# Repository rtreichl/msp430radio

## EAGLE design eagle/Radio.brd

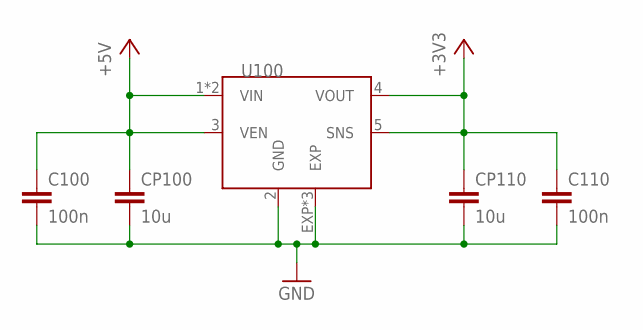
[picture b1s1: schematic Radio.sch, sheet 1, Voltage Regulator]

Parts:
C100, C110: 100n; C1206K
CP100, CP110: 10u; C1206K
U100: LP38693; LP38693_WSON

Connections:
+3V3: C110.1, CP110.1, U100.4 (VOUT), U100.5 (SNS); also elsewhere on the board
+5V: C100.1, CP100.1, U100.1 (VIN), U100.3 (VEN), U100.6 (VIN); also elsewhere on the board
GND: C100.2, C110.2, CP100.2, CP110.2, U100.2 (GND), U100.EXP, U100.EXP1 (EXP), U100.EXP2 (EXP); also elsewhere on the board

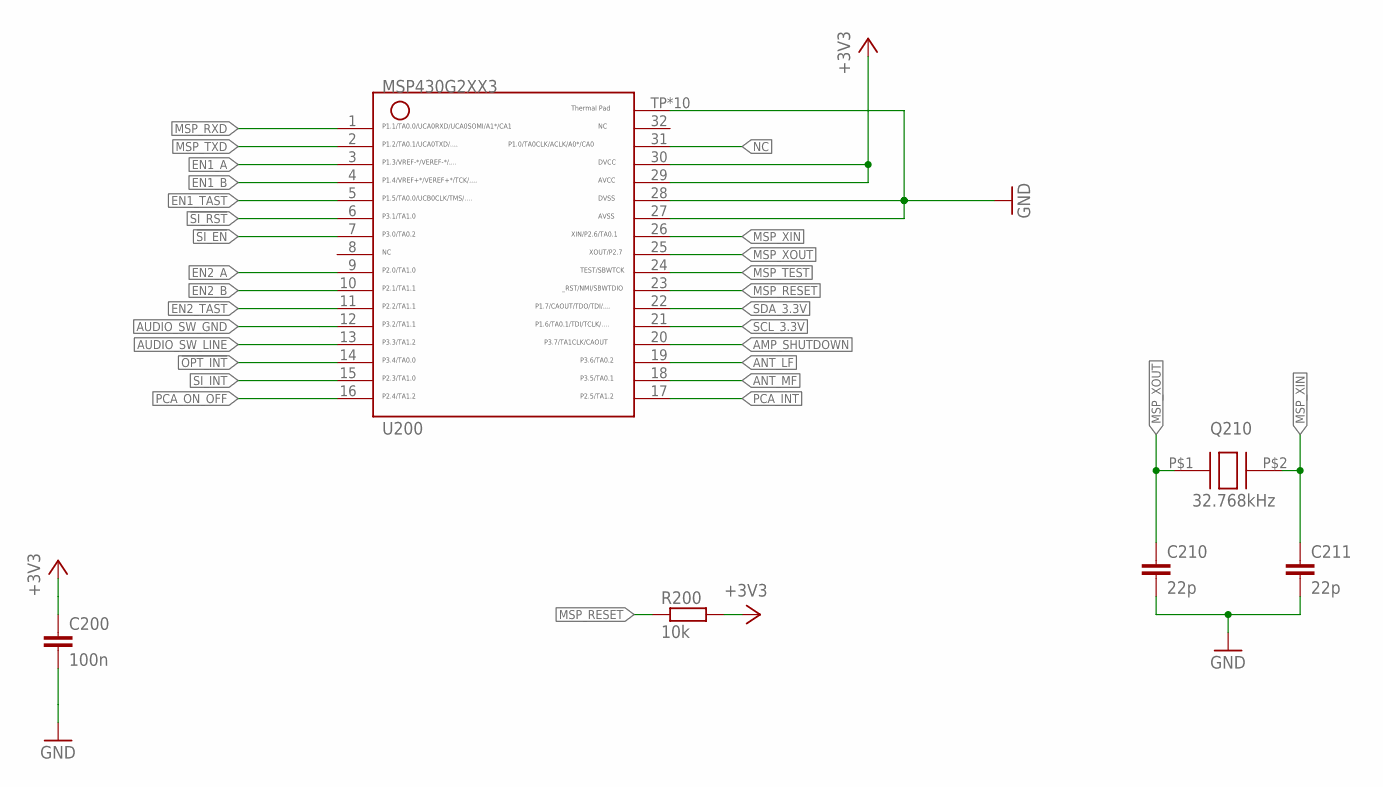
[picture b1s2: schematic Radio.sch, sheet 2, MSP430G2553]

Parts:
C200: 100n; C1206K
C210, C211: 22p; C1206K
Q210: 32.768kHz; CM7V-T1A
R200: 10k; R1206
U200: MSP430G2553; RHB32

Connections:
!OPT_INT: U200.14; also elsewhere on the board
!SI_EN: U200.7; also elsewhere on the board
!SI_RST: U200.6; also elsewhere on the board
+3V3: C200.1, R200.2, U200.29, U200.30; also elsewhere on the board
AMP_SHUTDOWN: U200.20; also elsewhere on the board
ANT_LF: U200.19; also elsewhere on the board
ANT_MF: U200.18; also elsewhere on the board
AUDIO_SW_GND: U200.12; also elsewhere on the board
AUDIO_SW_LINE: U200.13; also elsewhere on the board
EN1_A: U200.3; also elsewhere on the board
EN1_B: U200.4; also elsewhere on the board
EN1_TAST: U200.5; also elsewhere on the board
EN2_A: U200.9; also elsewhere on the board
EN2_B: U200.10; also elsewhere on the board
EN2_TAST: U200.11; also elsewhere on the board
GND: C200.2, C210.2, C211.2, U200.27, U200.28, U200.TP, U200.TP1 (TP), U200.TP2 (TP), U200.TP3 (TP), U200.TP4 (TP), U200.TP5 (TP), U200.TP6 (TP), U200.TP7 (TP), U200.TP8 (TP), U200.TP9 (TP); also elsewhere on the board
MSP_RESET: R200.1, U200.23; also elsewhere on the board
MSP_RXD: U200.1; also elsewhere on the board
MSP_TEST: U200.24; also elsewhere on the board
MSP_TXD: U200.2; also elsewhere on the board
MSP_XIN: C211.1, Q210.P$2 (2), U200.26
MSP_XOUT: C210.1, Q210.P$1 (1), U200.25
NC: U200.31
PCA_INT: U200.17; also elsewhere on the board
PCA_ON_OFF: U200.16; also elsewhere on the board
SCL_3.3V: U200.21; also elsewhere on the board
SDA_3.3V: U200.22; also elsewhere on the board
SI_INT: U200.15; also elsewhere on the board

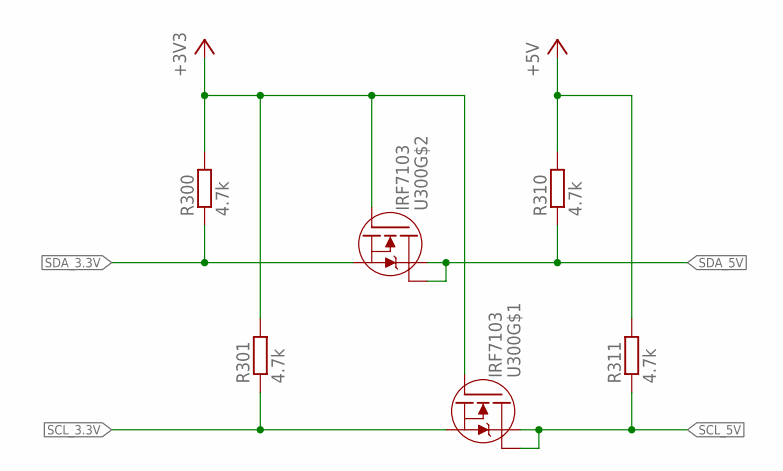
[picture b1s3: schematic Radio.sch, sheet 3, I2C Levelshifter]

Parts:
R300, R301, R310, R311: 4.7k; R1206
U300: IRF7103; SO8-2

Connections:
+3V3: R300.2, R301.2, U300.2 (G), U300.4 (G); also elsewhere on the board
+5V: R310.2, R311.2; also elsewhere on the board
SCL_3.3V: R301.1, U300.1 (S); also elsewhere on the board
SCL_5V: R311.1, U300.7 (D), U300.8 (D); also elsewhere on the board
SDA_3.3V: R300.1, U300.3 (S); also elsewhere on the board
SDA_5V: R310.1, U300.5 (D), U300.6 (D); also elsewhere on the board

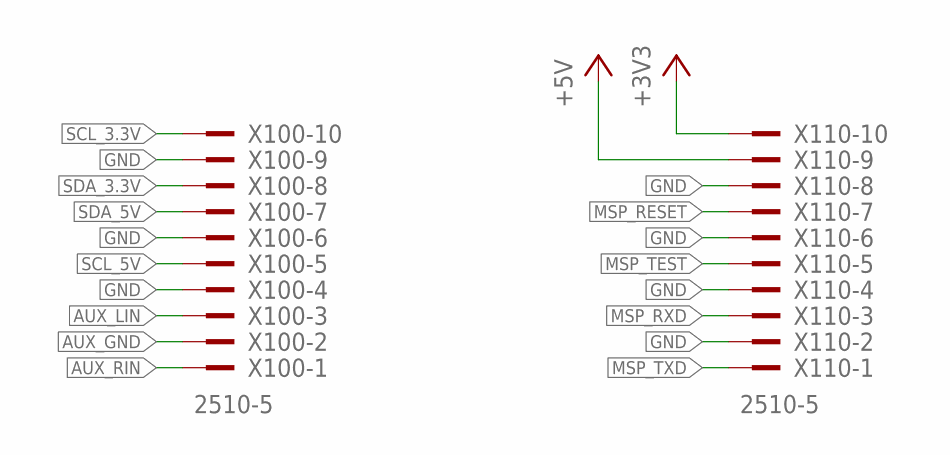
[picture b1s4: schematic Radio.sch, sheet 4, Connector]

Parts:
X100, X110: 2510-5; PAK100/2500-5-10

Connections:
+3V3: X110.10; also elsewhere on the board
+5V: X110.9; also elsewhere on the board
AUX_GND: X100.2; also elsewhere on the board
AUX_LIN: X100.3; also elsewhere on the board
AUX_RIN: X100.1; also elsewhere on the board
GND: X100.4, X100.6, X100.9, X110.2, X110.4, X110.6, X110.8; also elsewhere on the board
MSP_RESET: X110.7; also elsewhere on the board
MSP_RXD: X110.3; also elsewhere on the board
MSP_TEST: X110.5; also elsewhere on the board
MSP_TXD: X110.1; also elsewhere on the board
SCL_3.3V: X100.10; also elsewhere on the board
SCL_5V: X100.5; also elsewhere on the board
SDA_3.3V: X100.8; also elsewhere on the board
SDA_5V: X100.7; also elsewhere on the board

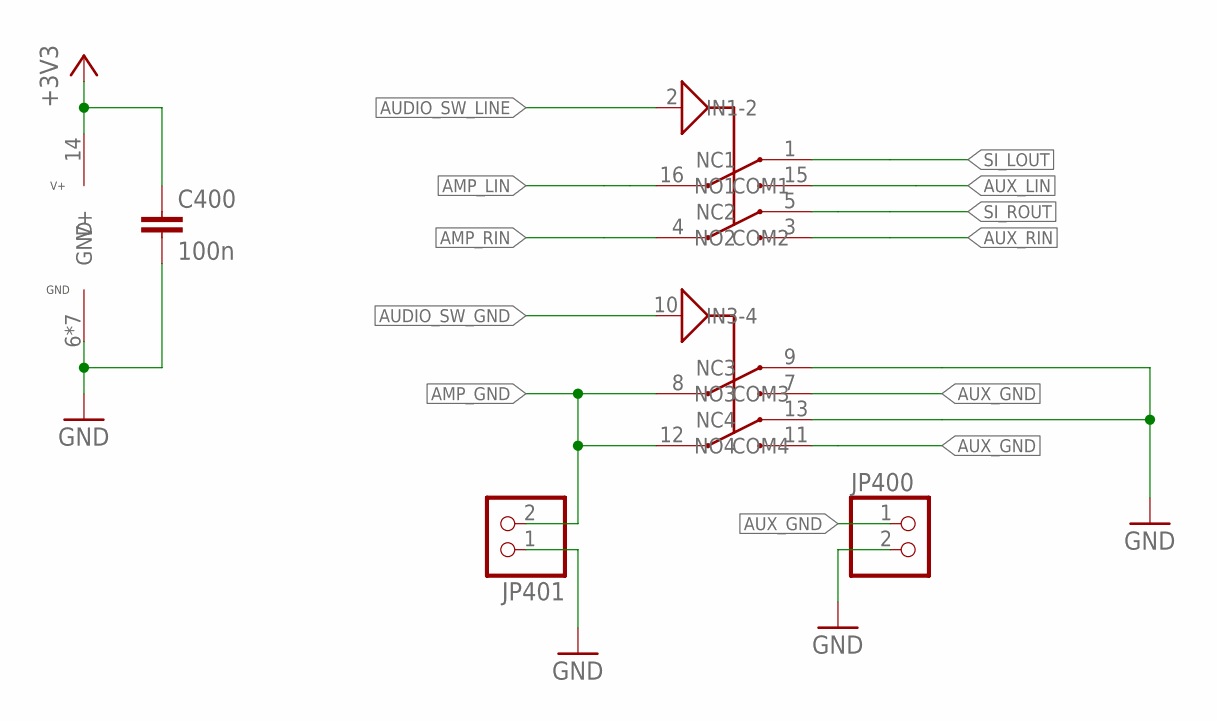
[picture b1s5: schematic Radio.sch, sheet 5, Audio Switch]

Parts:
C400: 100n; C1206K
JP400, JP401: PINHD-1X2; 1X02
U400: TS3A44159RGT; QFN16

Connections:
+3V3: C400.1, U400.14 (V+); also elsewhere on the board
AMP_GND: JP401.2, U400.8 (COM3), U400.12 (COM4); also elsewhere on the board
AMP_LIN: U400.16 (COM1); also elsewhere on the board
AMP_RIN: U400.4 (COM2); also elsewhere on the board
AUDIO_SW_GND: U400.10 (IN3-4); also elsewhere on the board
AUDIO_SW_LINE: U400.2 (IN1-2); also elsewhere on the board
AUX_GND: JP400.1, U400.7 (NO3), U400.11 (NO4); also elsewhere on the board
AUX_LIN: U400.15 (NO1); also elsewhere on the board
AUX_RIN: U400.3 (NO2); also elsewhere on the board
GND: C400.2, JP400.2, JP401.1, U400.6 (GND), U400.9 (NC3), U400.13 (NC4), U400.TH (GND), U400.TH1 (GND), U400.TH2 (GND), U400.TH3 (GND), U400.TH4 (GND), U400.TH5 (GND); also elsewhere on the board
SI_LOUT: U400.1 (NC1); also elsewhere on the board
SI_ROUT: U400.5 (NC2); also elsewhere on the board

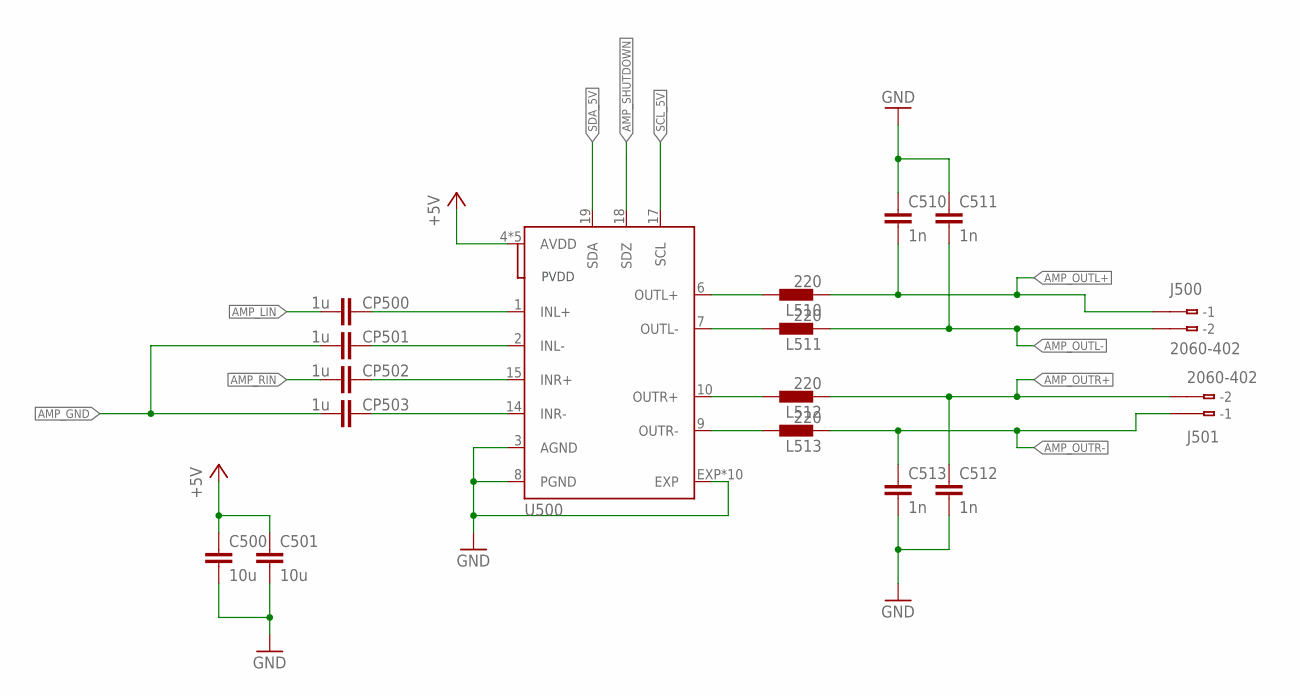
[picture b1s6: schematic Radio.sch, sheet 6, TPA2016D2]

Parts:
C500, C501: 10u; C1206K
C510, C511, C512, C513: 1n; C1206K
CP500, CP501, CP502, CP503: 1u; C1206K
J500, J501: 2060-402; WAGO_2060-402
L510, L511, L512, L513: 220; R0603
U500: TPA2016D2; TPA2016D2_PWQFN-20

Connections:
+5V: C500.1, C501.1, U500.4 (AVDD), U500.5 (AVDD), U500.11 (AVDD), U500.12 (AVDD), U500.13 (AVDD); also elsewhere on the board
AMP_GND: CP501.2, CP503.2; also elsewhere on the board
AMP_LIN: CP500.2; also elsewhere on the board
AMP_OUTL+: C510.2, J500.B-1, L510.1; also elsewhere on the board
AMP_OUTL-: C511.2, J500.B-2, L511.1; also elsewhere on the board
AMP_OUTR+: C512.1, J501.B-2, L512.1; also elsewhere on the board
AMP_OUTR-: C513.1, J501.B-1, L513.1; also elsewhere on the board
AMP_RIN: CP502.2; also elsewhere on the board
AMP_SHUTDOWN: U500.18 (SDZ); also elsewhere on the board
GND: C500.2, C501.2, C510.1, C511.1, C512.2, C513.2, U500.3 (AGND), U500.8 (PGND), U500.EXP, U500.EXP1 (EXP), U500.EXP2 (EXP), U500.EXP3 (EXP), U500.EXP4 (EXP), U500.EXP5 (EXP), U500.EXP6 (EXP), U500.EXP7 (EXP), U500.EXP8 (EXP), U500.EXP9 (EXP); also elsewhere on the board
unnamed: L510.2, U500.6 (OUTL+)
unnamed: L511.2, U500.7 (OUTL-)
unnamed: L512.2, U500.10 (OUTR+)
unnamed: L513.2, U500.9 (OUTR-)
unnamed: CP500.1, U500.1 (INL+)
unnamed: CP502.1, U500.15 (INR+)
unnamed: CP501.1, U500.2 (INL-)
unnamed: CP503.1, U500.14 (INR-)
SCL_5V: U500.17 (SCL); also elsewhere on the board
SDA_5V: U500.19 (SDA); also elsewhere on the board

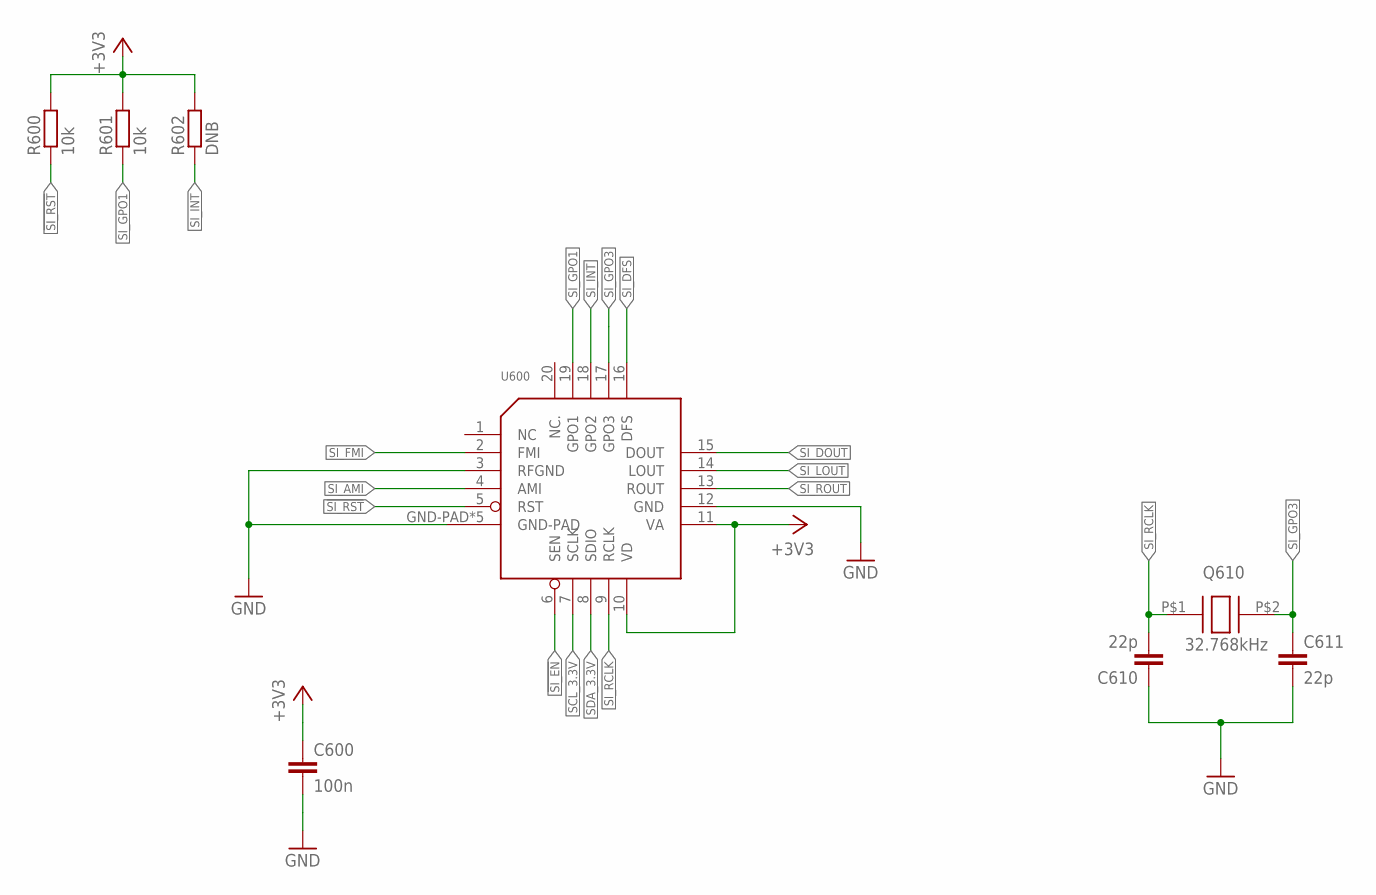
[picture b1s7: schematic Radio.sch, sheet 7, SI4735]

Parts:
C600: 100n; C1206K
C610, C611: 22p; C1206K
Q610: 32.768kHz; CM7V-T1A
R600, R601: 10k; R1206
R602: DNB; R1206
U600: SI473X-D60

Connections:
!SI_EN: U600.6 (SEN); also elsewhere on the board
!SI_RST: R600.1, U600.5 (RST); also elsewhere on the board
+3V3: C600.1, R600.2, R601.2, R602.2, U600.10 (VD), U600.11 (VA); also elsewhere on the board
GND: C600.2, C610.1, C611.2, U600.3 (RFGND), U600.12 (GND), U600.GND-PAD, U600.GND-PAD1 (GND-PAD), U600.GND-PAD2 (GND-PAD), U600.GND-PAD3 (GND-PAD), U600.GND-PAD4 (GND-PAD); also elsewhere on the board
SCL_3.3V: U600.7 (SCLK); also elsewhere on the board
SDA_3.3V: U600.8 (SDIO); also elsewhere on the board
SI_AMI: U600.4 (AMI); also elsewhere on the board
SI_DFS: U600.16 (DFS)
SI_DOUT: U600.15 (DOUT)
SI_FMI: U600.2 (FMI); also elsewhere on the board
SI_GPO1: R601.1, U600.19 (GPO1)
SI_GPO3: C611.1, Q610.P$2 (2), U600.17 (GPO3)
SI_INT: R602.1, U600.18 (GPO2); also elsewhere on the board
SI_LOUT: U600.14 (LOUT); also elsewhere on the board
SI_RCLK: C610.2, Q610.P$1 (1), U600.9 (RCLK)
SI_ROUT: U600.13 (ROUT); also elsewhere on the board

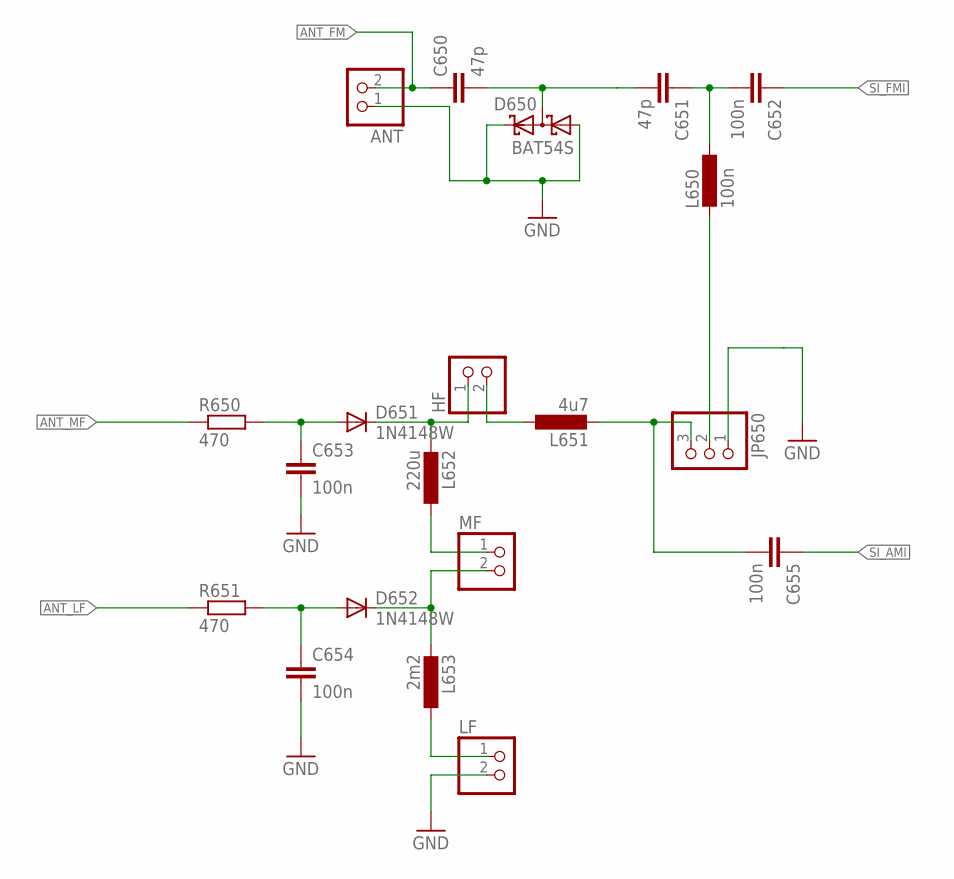
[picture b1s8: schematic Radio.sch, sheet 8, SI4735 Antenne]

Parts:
ANT: PINHD-1X2; 1X02
C650, C651: 47p; C1206K
C652, C653, C654, C655: 100n; C1206K
D650: BAT54S; SOT23
D651, D652: 1N4148W; SOD123
HF: PINHD-1X2; 1X02
JP650: PINHD-1X3; 1X03
L650: 100n; L1210
L651: 4u7; L1210
L652: 220u; L1210
L653: 2m2; L1812
LF: PINHD-1X2; 1X02
MF: PINHD-1X2; 1X02
R650, R651: 470; R1206

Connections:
ANT_FM: ANT.2, C650.1; also elsewhere on the board
ANT_LF: R651.1; also elsewhere on the board
ANT_MF: R650.1; also elsewhere on the board
GND: ANT.1, C653.2, C654.2, D650.1 (A1), D650.2 (C2), JP650.1, LF.2; also elsewhere on the board
unnamed: C650.2, C651.2, D650.3 (C1A2)
unnamed: HF.2, L651.1
unnamed: JP650.2, L650.2
unnamed: C655.2, JP650.3, L651.2
unnamed: D651.C, HF.1, L652.2
unnamed: D652.C, L653.2, MF.2
unnamed: C654.1, D652.A, R651.2
unnamed: C653.1, D651.A, R650.2
unnamed: L653.1, LF.1
unnamed: L652.1, MF.1
unnamed: C651.1, C652.2, L650.1
SI_AMI: C655.1; also elsewhere on the board
SI_FMI: C652.1; also elsewhere on the board

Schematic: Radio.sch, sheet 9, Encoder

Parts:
C800, C801, C802, C810, C811, C812: 10n; C1206K
EN800, EN810: PEC11R
R800, R801, R802, R803, R804, R805, R810, R811, R812, R813, R814, R815: 10k; R1206

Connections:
+3V3: R801.2, R803.2, R804.2, R811.1, R813.2, R814.2; also elsewhere on the board
EN1_A: C801.1, R802.2; also elsewhere on the board
EN1_B: C802.1, R805.2; also elsewhere on the board
EN1_TAST: C800.2, R800.1; also elsewhere on the board
EN2_A: C811.1, R812.2; also elsewhere on the board
EN2_B: C812.1, R815.2; also elsewhere on the board
EN2_TAST: C810.1, R810.2; also elsewhere on the board
GND: C800.1, C801.2, C802.2, C810.2, C811.2, C812.2, EN800.C, EN800.W, EN810.C, EN810.W; also elsewhere on the board
unnamed: EN810.A, R812.1, R813.1
unnamed: EN800.A, R802.1, R803.1
unnamed: EN810.B, R814.1, R815.1
unnamed: EN800.S, R800.2, R801.1
unnamed: EN810.S, R810.1, R811.2
R904: EN800.B, R804.1, R805.1

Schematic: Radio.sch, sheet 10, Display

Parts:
C900, C903, C930: 1u; C1206K
C901, C910, C920: 100n; C1206K
J920, J921: 2060-402; WAGO_2060-402
Q900: BSS123; SOT23
R900: 4R7; R1206
R901, R921, R922, R923, R930: 1k; R1206
U900: EA_DOGMXXX-A
U910: PCA8574; PCA8574_TSSOP16
U920: PCA9632TK; TSSOP8
U930: IRF7309; SO8-2

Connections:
+5V: C900.1, C901.1, C903.1, C930.1, J921.B-1, R930.2, U900.20 (LED2+), U900.23 (PSB), U900.24 (VOUT), U900.25 (VIN), U900.26 (VDD), U900.32 (D3), U900.33 (D2), U900.34 (D1), U900.35 (D0), U900.40 (RESET), U930.3 (S); also elsewhere on the board
+5_PCA: C910.1, C920.1, U910.16 (VDD), U920.8 (VDD), U930.5 (D), U930.6 (D)
GND: C900.2, C901.2, C903.2, C910.2, C920.2, C930.2, Q900.2 (S), R901.1, U900.27 (VSS), U900.38 (CS), U910.1 (A0), U910.2 (A1), U910.3 (A2), U910.8 (GND), U920.5 (VSS), U930.1 (S); also elsewhere on the board
LCD_BACKLIGHT: Q900.1 (G), R901.2, U920.1 (LED0); also elsewhere on the board
unnamed: R930.1, U930.4 (G), U930.7 (D), U930.8 (D)
unnamed: R923.1, U920.4 (LED3)
unnamed: Q900.3 (D), R900.2
unnamed: R922.1, U920.3 (LED2)
unnamed: U900.31 (D4), U910.4 (P0)
unnamed: U900.30 (D5), U910.5 (P1)
unnamed: U900.29 (D6), U910.6 (P2)
unnamed: U900.28 (D7), U910.7 (P3)
unnamed: U900.36 (E), U910.9 (P4)
unnamed: U900.37 (R/W), U910.10 (P5)
unnamed: U900.39 (RS), U910.11 (P6)
unnamed: R921.1, U920.2 (LED1)
unnamed: U900.1 (LED1+), U900.19 (LED2-)
unnamed: R900.1, U900.2 (LED1-)
unnamed: J920.B-1, R921.2
unnamed: J920.B-2, R922.2
unnamed: J921.B-2, R923.2
PCA_INT: U910.13 (INT); also elsewhere on the board
PCA_ON_OFF: U930.2 (G); also elsewhere on the board
SCL_5V: U910.14 (SCL), U920.6 (SCL); also elsewhere on the board
SDA_5V: U910.15 (SDA), U920.7 (SDA); also elsewhere on the board

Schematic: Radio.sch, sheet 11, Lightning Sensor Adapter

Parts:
C940: 100n; C1206K
U940: OPT3001; SON65P200X200X65-7T66X136N

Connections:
!OPT_INT: U940.5 (!INT); also elsewhere on the board
+3V3: C940.1, U940.1 (VDD); also elsewhere on the board
GND: C940.2, U940.2 (ADDR), U940.3 (GND), U940.7 (EXP); also elsewhere on the board
SCL_3.3V: U940.4 (SCL); also elsewhere on the board
SDA_3.3V: U940.6 (SDA); also elsewhere on the board

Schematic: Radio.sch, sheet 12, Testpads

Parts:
TP1, TP2, TP3, TP9, TP10, TP11, TP12, TP13, TP14, TP15, TP16, TP17, TP18, TP19, TP20, TP21, TP27, TP28, TP32, TP33, TP34, TP35: PTR1B1,27; B1,27
TP4, TP5, TP6, TP7, TP8, TP22, TP23, TP24, TP25, TP26, TP29, TP30, TP31: PTR1B2,54; B2,54

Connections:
+3V3: TP1.TP, TP32.TP, TP33.TP; also elsewhere on the board
+5V: TP2.TP, TP3.TP, TP29.TP, TP31.TP; also elsewhere on the board
AMP_LIN: TP16.TP; also elsewhere on the board
AMP_OUTL+: TP25.TP; also elsewhere on the board
AMP_OUTL-: TP26.TP; also elsewhere on the board
AMP_OUTR+: TP23.TP; also elsewhere on the board
AMP_OUTR-: TP24.TP; also elsewhere on the board
AMP_RIN: TP17.TP; also elsewhere on the board
ANT_FM: TP13.TP; also elsewhere on the board
AUX_GND: TP35.TP; also elsewhere on the board
AUX_LIN: TP14.TP; also elsewhere on the board
AUX_RIN: TP15.TP; also elsewhere on the board
GND: TP4.TP, TP5.TP, TP6.TP, TP7.TP, TP8.TP, TP22.TP, TP30.TP; also elsewhere on the board
LCD_BACKLIGHT: TP34.TP; also elsewhere on the board
MSP_RESET: TP20.TP; also elsewhere on the board
MSP_RXD: TP18.TP; also elsewhere on the board
MSP_TEST: TP21.TP; also elsewhere on the board
MSP_TXD: TP19.TP; also elsewhere on the board
SCL_3.3V: TP10.TP; also elsewhere on the board
SCL_5V: TP28.TP; also elsewhere on the board
SDA_3.3V: TP9.TP; also elsewhere on the board
SDA_5V: TP27.TP; also elsewhere on the board
SI_LOUT: TP11.TP; also elsewhere on the board
SI_ROUT: TP12.TP; also elsewhere on the board

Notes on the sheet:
Testpads

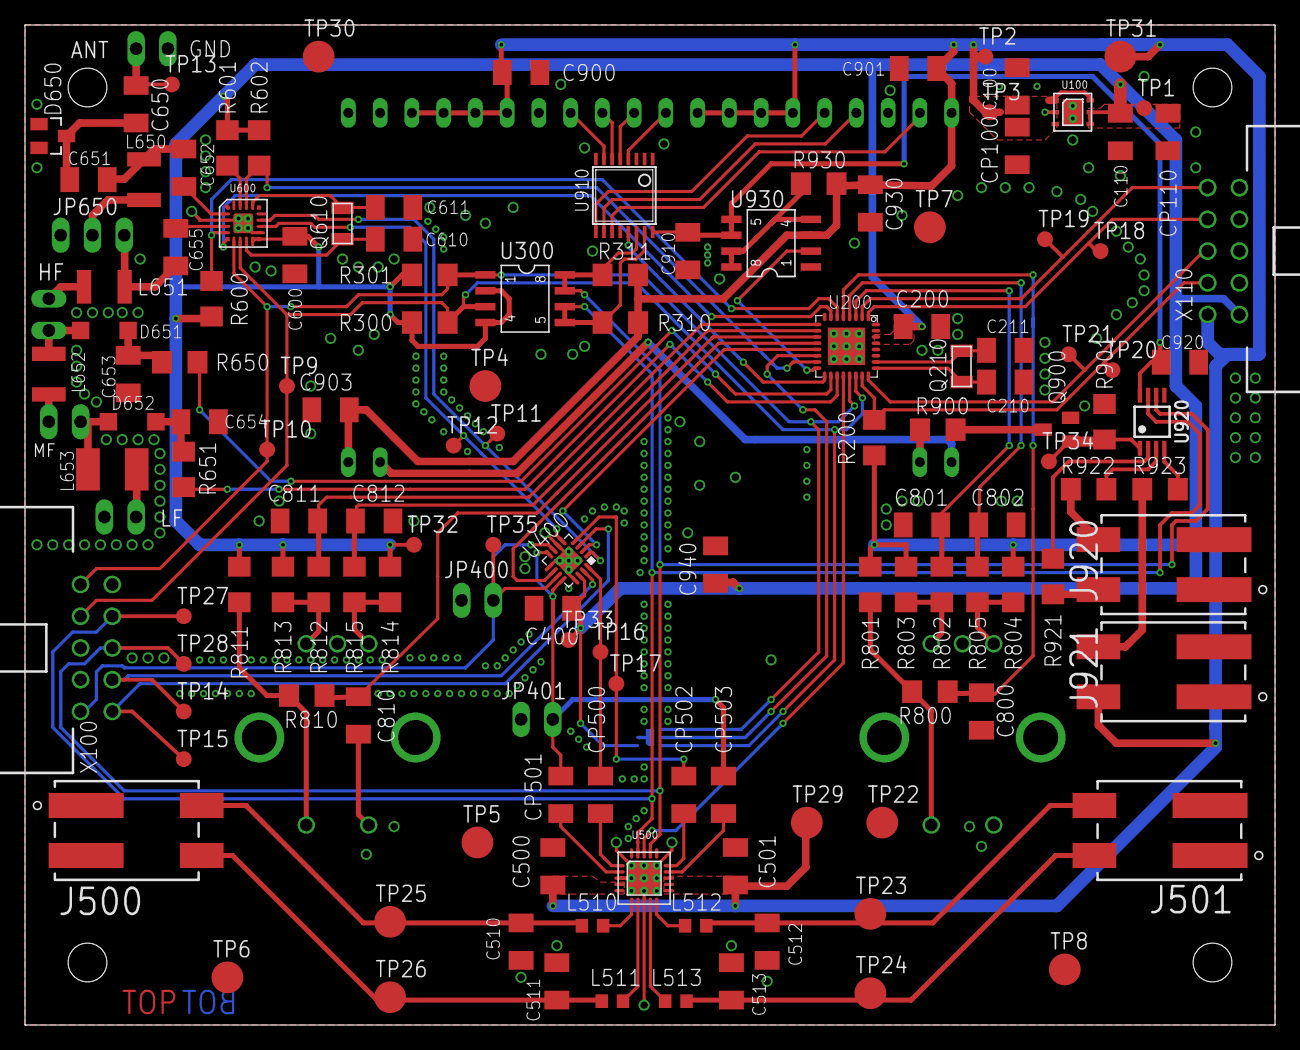
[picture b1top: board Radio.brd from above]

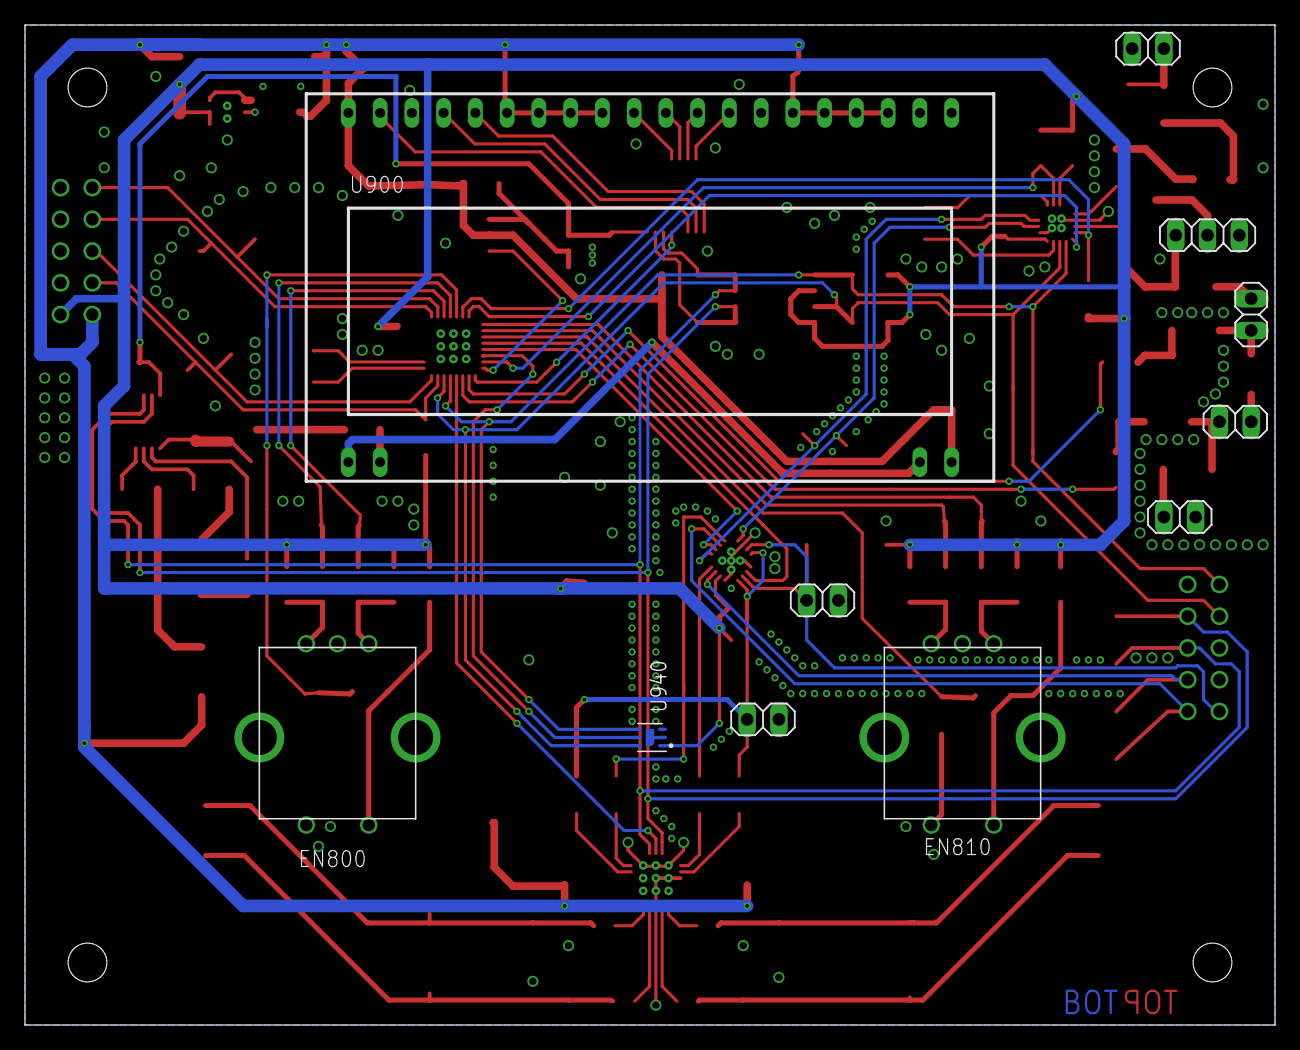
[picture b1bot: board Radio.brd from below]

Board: 2 copper layers, 100.0 x 80.0 mm, 143 parts (11 on the bottom side), 92 nets.

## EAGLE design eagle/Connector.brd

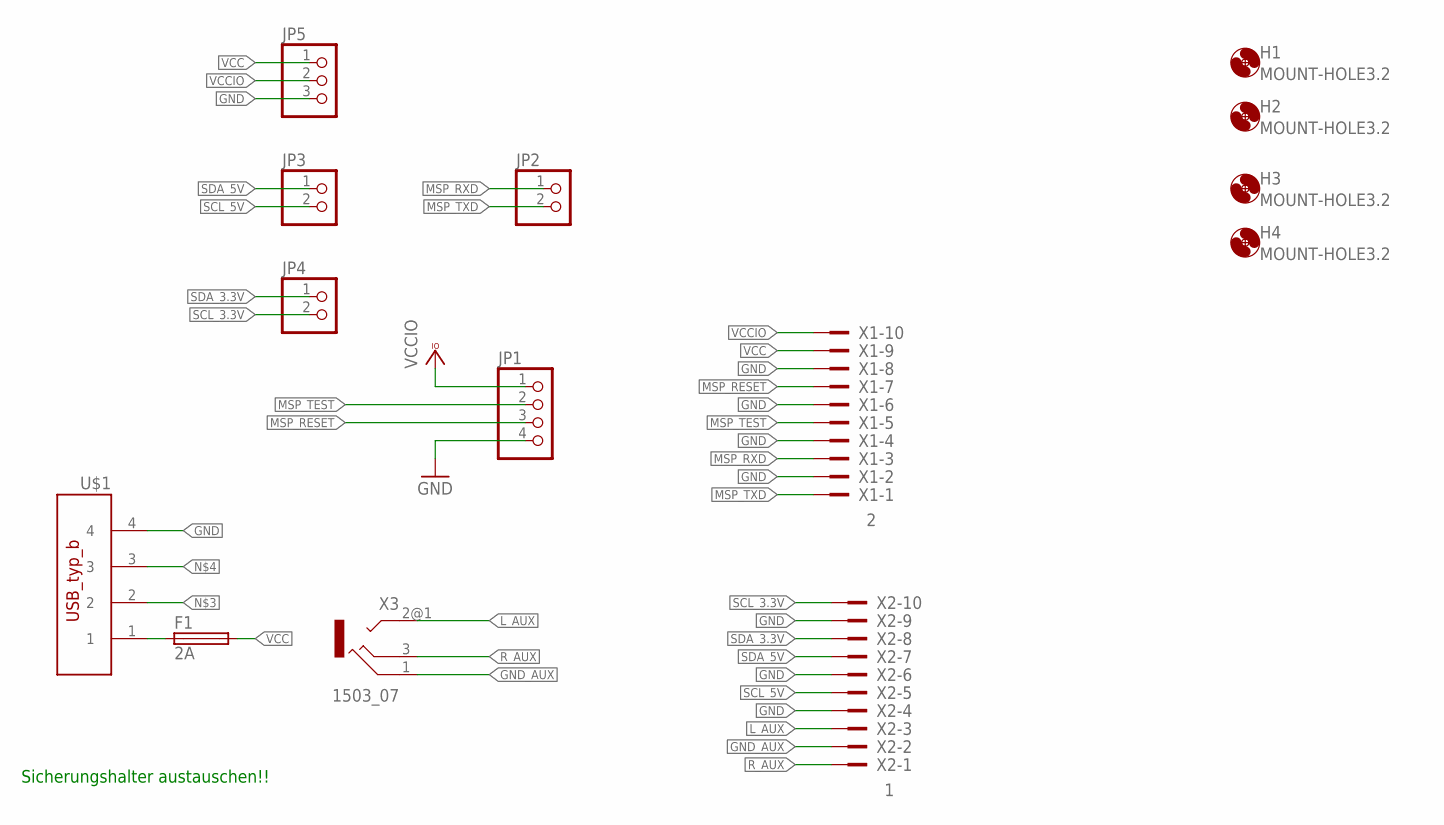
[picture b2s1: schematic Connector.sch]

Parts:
F1: 2A; SH22,5A
H1, H2, H3, H4: MOUNT-HOLE3.2; 3,2
JP1: PINHD-1X4; 1X04
JP2, JP3, JP4: PINHD-1X2; 1X02
JP5: PINHD-1X3; 1X03
U$1: USB_TYP_B
X1: 2; PAK100/2500-10
X2: 1; PAK100/2500-10
X3: 1503_07

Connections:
GND: JP1.4, JP5.3, U$1.4, X1.2, X1.4, X1.6, X1.8, X2.4, X2.6, X2.9
GND_AUX: X2.2, X3.1
L_AUX: X2.3, X3.2@1 (2)
MSP_RESET: JP1.3, X1.7
MSP_RXD: JP2.1, X1.3
MSP_TEST: JP1.2, X1.5
MSP_TXD: JP2.2, X1.1
unnamed: F1.1, U$1.1
R_AUX: X2.1, X3.3
SCL_3.3V: JP4.2, X2.10
SCL_5V: JP3.2, X2.5
SDA_3.3V: JP4.1, X2.8
SDA_5V: JP3.1, X2.7
VCC: F1.2, JP5.1, X1.9
VCCIO: JP1.1, JP5.2, X1.10

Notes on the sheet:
Sicherungshalter austauschen!!

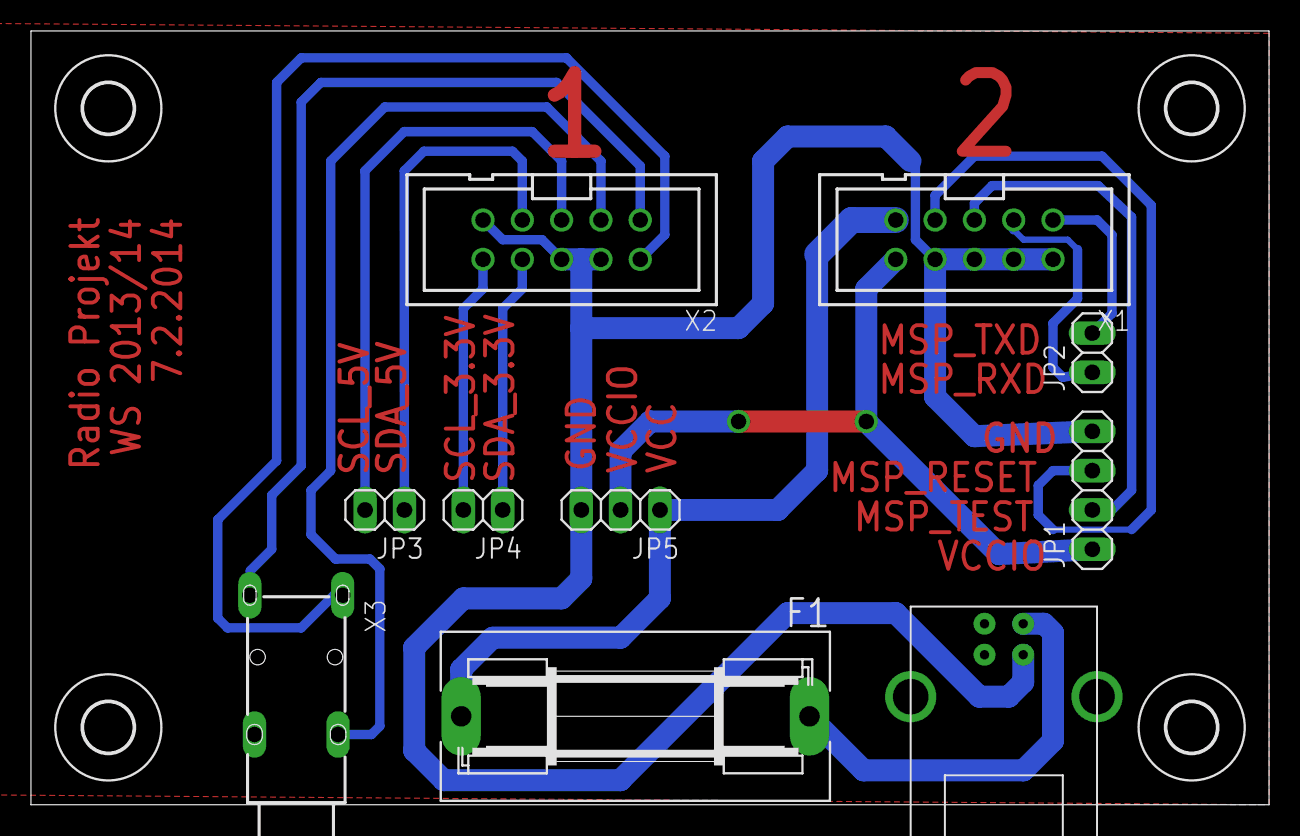
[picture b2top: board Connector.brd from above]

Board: 2 copper layers, 80.0 x 50.0 mm, 14 parts (0 on the bottom side), 15 nets.

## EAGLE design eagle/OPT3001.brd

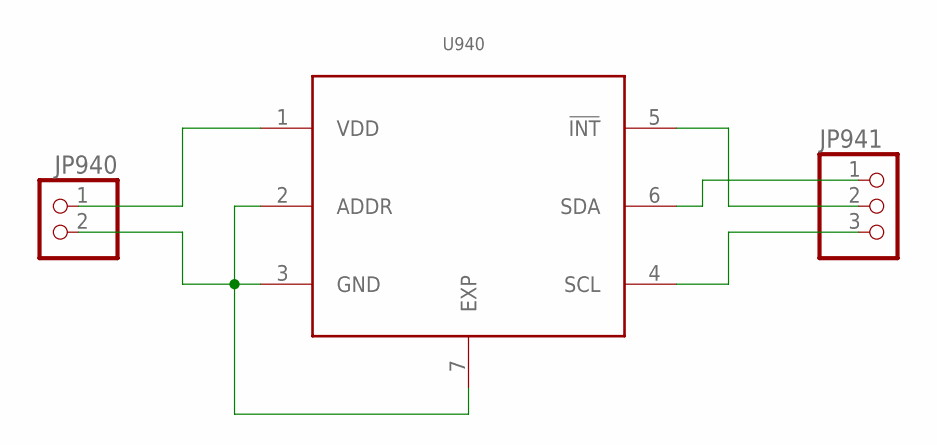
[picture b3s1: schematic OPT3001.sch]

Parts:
JP940: PINHD-1X2; 1X02
JP941: PINHD-1X3; 1X03
U940: OPT3001; SON65P200X200X65-7T66X136N

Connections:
unnamed: JP940.1, U940.1 (VDD)
unnamed: JP940.2, U940.2 (ADDR), U940.3 (GND), U940.7 (EXP)
unnamed: JP941.2, U940.5 (!INT)
unnamed: JP941.1, U940.6 (SDA)
unnamed: JP941.3, U940.4 (SCL)

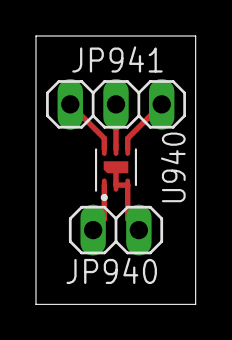
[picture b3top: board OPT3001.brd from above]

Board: 2 copper layers, 8.9 x 14.9 mm, 3 parts (0 on the bottom side), 5 nets.

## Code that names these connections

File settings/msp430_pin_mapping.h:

//----------------------------------------------------------------------------------------
//
/// \brief	Definition for the Pins of the MSP430
//
//----------------------------------------------------------------------------------------

#define MSP_RXD			1.1
#define MSP_TXD			1.2
#define EN1_A			1.3
#define EN1_B			1.4
#define EN1_TAST		1.5
#define SI_RST			3.1
#define SI_INT			2.3
#define SI_EN			3.0
#define EN2_A			2.0
#define EN2_B			2.1
#define EN2_TAST		2.2
#define AUDIO_SW_GND	3.2
#define AUDIO_SW_LINE	3.3
#define PCA_ON_OFF		2.4
#define PCA_INT			2.5
#define ANT_MF			3.5
#define ANT_LF			3.6
#define AMP_SHUTDOWN	3.7
#define SCL				1.6
#define SDA				1.7
#define PWM_RST			1.0

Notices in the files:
parts and their libraries:
irf-2: Copyright & License
This library is licensed under the General Public License, Version 2.
More Information about the General Public License is available at http://www.gnu.org/copyleft/gpl.html.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
